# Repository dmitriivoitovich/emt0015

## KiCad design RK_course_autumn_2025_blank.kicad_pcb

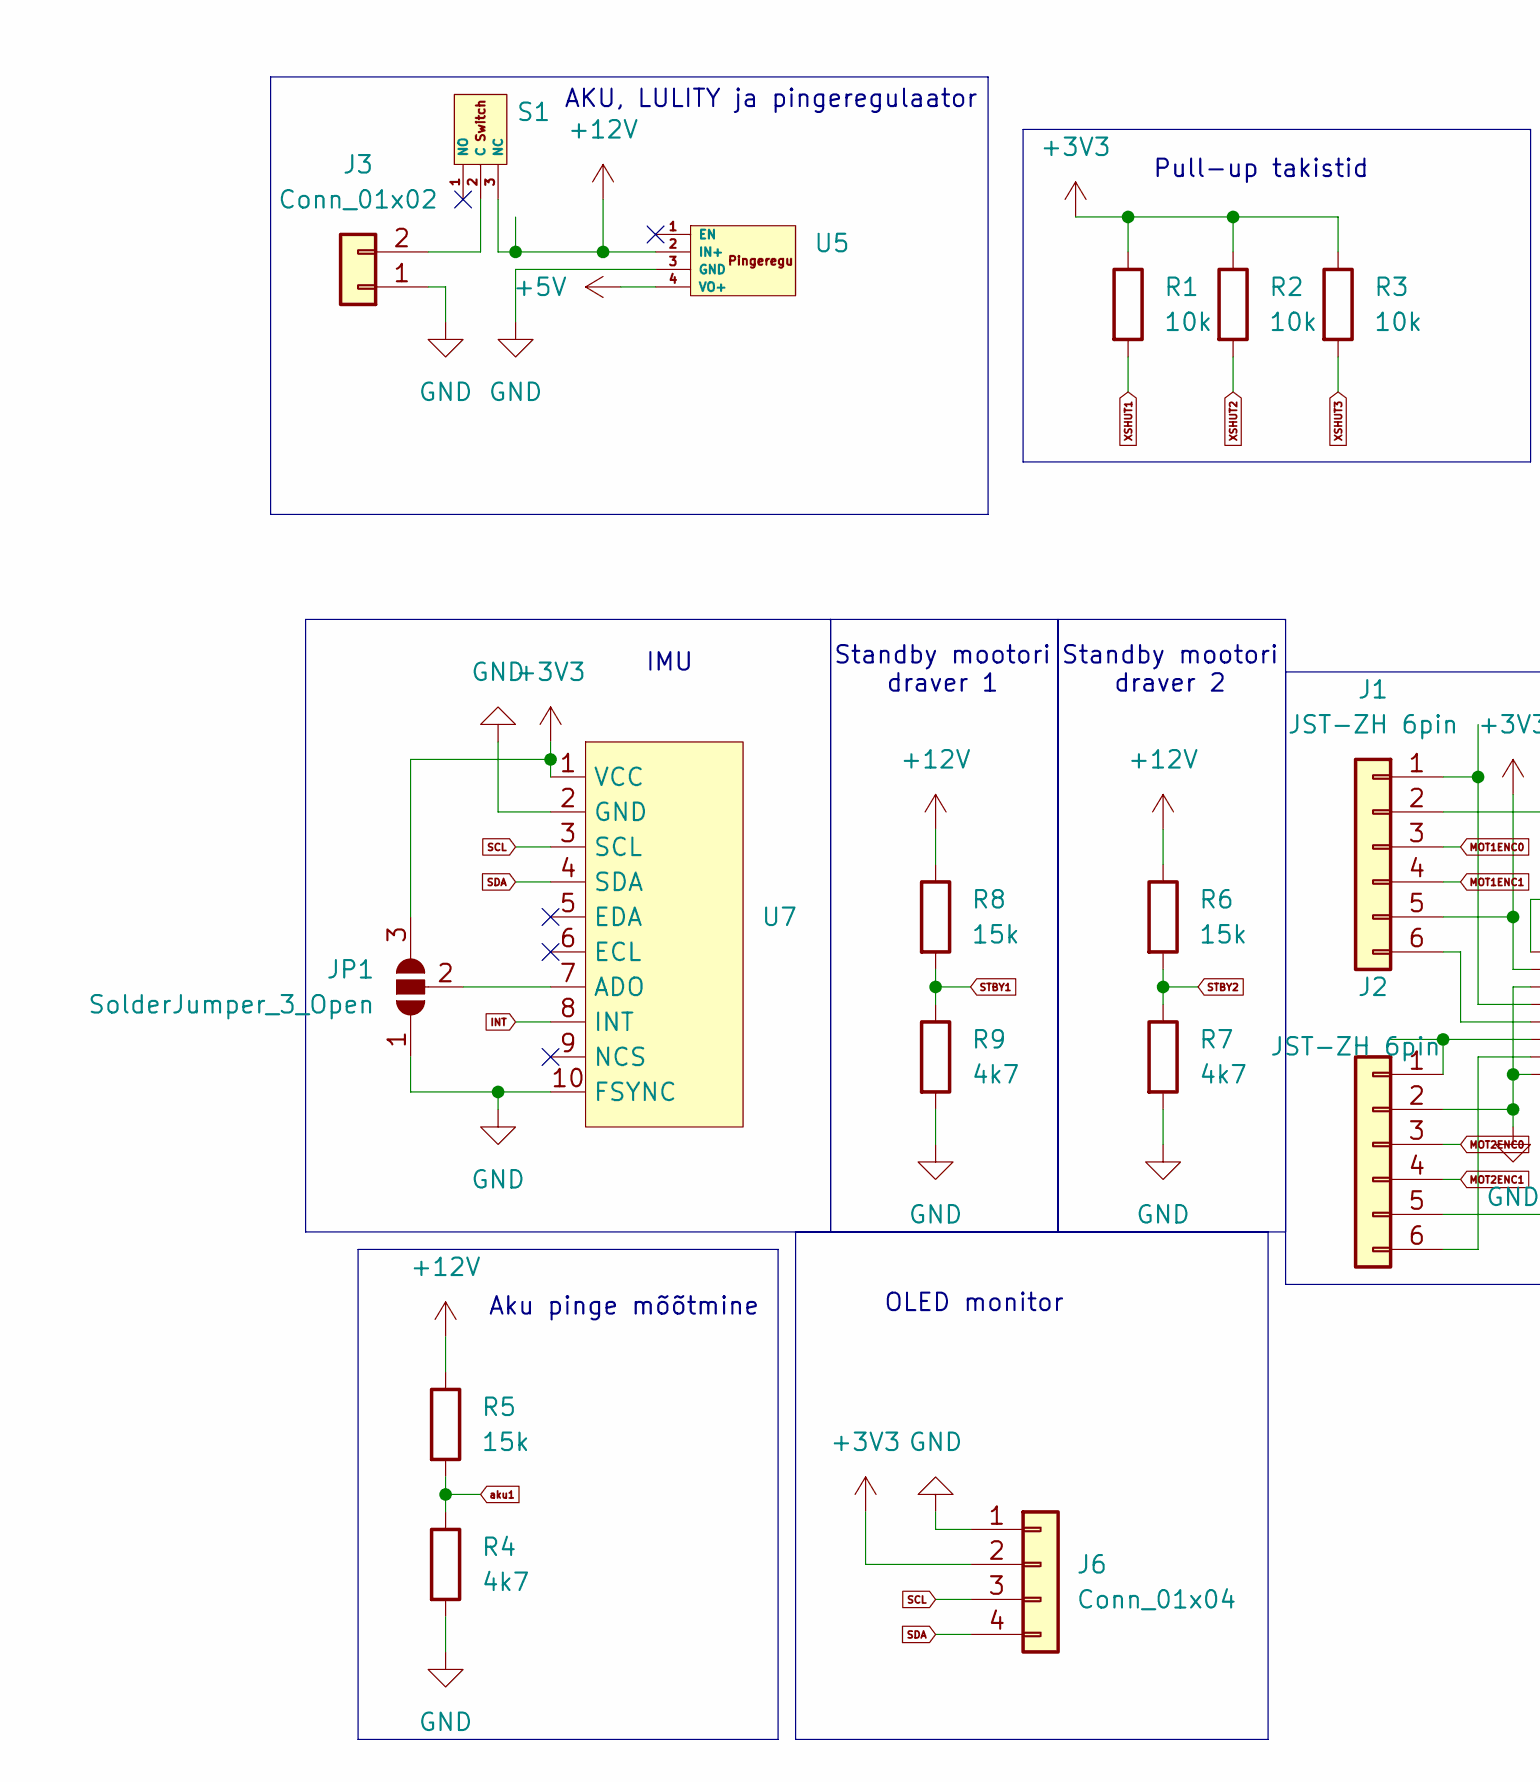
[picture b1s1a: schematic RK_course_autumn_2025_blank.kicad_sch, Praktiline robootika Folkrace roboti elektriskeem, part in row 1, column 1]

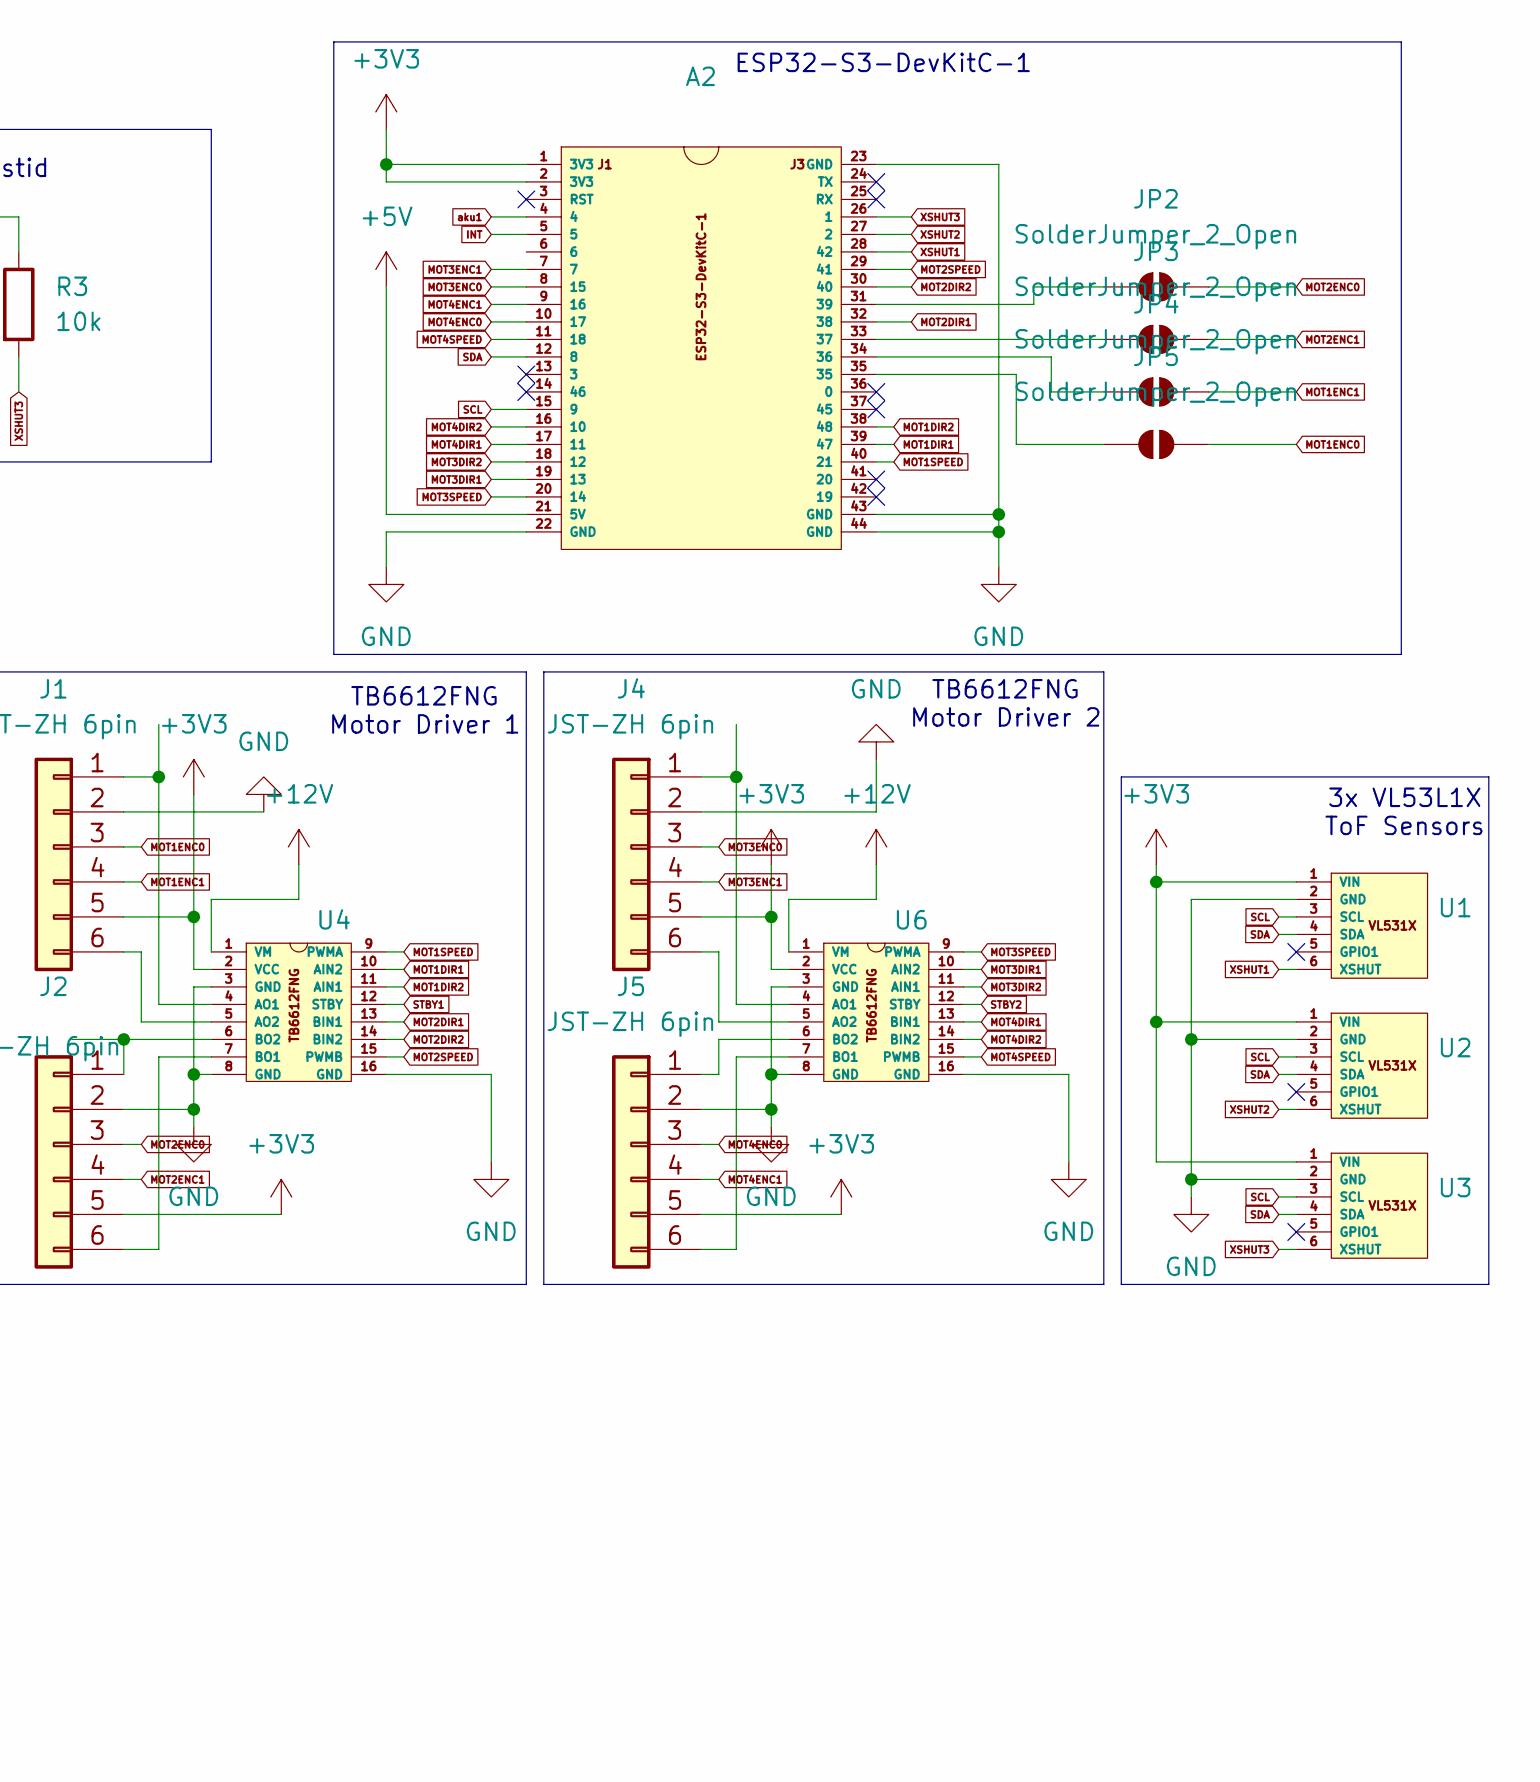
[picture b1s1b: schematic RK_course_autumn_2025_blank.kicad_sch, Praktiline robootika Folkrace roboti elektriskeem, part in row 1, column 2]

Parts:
A2: ESP32-S3-DevKitC-1
J1, J2, J4, J5: JST-ZH 6pin; JST_ZH_B6B-ZR_1x06_P1.50mm_Vertical
J3: Conn_01x02; AMASS_XT30PW-M_1x02_P2.50mm_Horizontal
J6: Conn_01x04; PinHeader_1x04_P2.54mm_Vertical
JP1: SolderJumper_3_Open; SolderJumper-3_P1.3mm_Open_RoundedPad1.0x1.5mm
JP2, JP3, JP4, JP5: SolderJumper_2_Open; SolderJumper-2_P1.3mm_Open_RoundedPad1.0x1.5mm
R1, R2, R3: 10k; R_0603_1608Metric_Pad0.98x0.95mm_HandSolder
R4, R7, R9: 4k7; R_0603_1608Metric_Pad0.98x0.95mm_HandSolder
R5, R6, R8: 15k; R_0603_1608Metric_Pad0.98x0.95mm_HandSolder
S1: 6A125VAC_NO-NO_SWITCH
U1, U2, U3: VL531X_KAUGUS_SENSOR
U4, U6: TB6612FNG_DUAL_MOTOR_DRIVER_RED
U5: PINGEREGU
U7: IMU

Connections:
+3V3: A2.1 (3V3), A2.2 (3V3), J1.5, J2.5, J4.5, J5.5, J6.2, JP1.3 (B), R1.1, R2.1, R3.1, U1.1 (VIN), U2.1 (VIN), U3.1 (VIN), U4.2 (VCC), U6.2 (VCC), U7.1 (VCC)
+5V: A2.21 (5V), U5.4 (VO+)
+12V: R5.1, R6.1, R8.1, S1.3 (NC), U4.1 (VM), U5.2 (IN+), U6.1 (VM)
GND: A2.22 (GND), A2.23 (GND), A2.43 (GND), A2.44 (GND), J1.2, J2.2, J3.1, J4.2, J5.2, J6.1, JP1.1 (A), R4.2, R7.2, R9.2, U1.2 (GND), U2.2 (GND), U3.2 (GND), U4.3 (GND), U4.8 (GND), U4.16 (GND), U5.3 (GND), U6.3 (GND), U6.8 (GND), U6.16 (GND), U7.2 (GND), U7.10 (FSYNC)
INT: A2.5, U7.8 (INT)
MOT1DIR1: A2.39 (47), U4.10 (AIN2)
MOT1DIR2: A2.38 (48), U4.11 (AIN1)
MOT1ENC0: J1.3, JP5.2 (B)
MOT1ENC1: J1.4, JP4.2 (B)
MOT1SPEED: A2.40 (21), U4.9 (PWMA)
MOT2DIR1: A2.32 (38), U4.13 (BIN1)
MOT2DIR2: A2.30 (40), U4.14 (BIN2)
MOT2ENC0: J2.3, JP2.2 (B)
MOT2ENC1: J2.4, JP3.2 (B)
MOT2SPEED: A2.29 (41), U4.15 (PWMB)
MOT3DIR1: A2.19 (13), U6.10 (AIN2)
MOT3DIR2: A2.18 (12), U6.11 (AIN1)
MOT3ENC0: A2.8 (15), J4.3
MOT3ENC1: A2.7, J4.4
MOT3SPEED: A2.20 (14), U6.9 (PWMA)
MOT4DIR1: A2.17 (11), U6.13 (BIN1)
MOT4DIR2: A2.16 (10), U6.14 (BIN2)
MOT4ENC0: A2.10 (17), J5.3
MOT4ENC1: A2.9 (16), J5.4
MOT4SPEED: A2.11 (18), U6.15 (PWMB)
unnamed: A2.34 (36), JP4.1 (A)
unnamed: A2.33 (37), JP3.1 (A)
unnamed: A2.31 (39), JP2.1 (A)
unnamed: J1.1, U4.4 (AO1)
unnamed: J1.6, U4.5 (AO2)
unnamed: J2.1, U4.6 (BO2)
unnamed: J2.6, U4.7 (BO1)
unnamed: J3.2, S1.2 (C)
unnamed: J4.1, U6.4 (AO1)
unnamed: J4.6, U6.5 (AO2)
unnamed: J5.1, U6.6 (BO2)
unnamed: J5.6, U6.7 (BO1)
unnamed: JP1.2 (C), U7.7 (ADO)
unnamed: A2.35, JP5.1 (A)
SCL: A2.15 (9), J6.3, U1.3 (SCL), U2.3 (SCL), U3.3 (SCL), U7.3 (SCL)
SDA: A2.12 (8), J6.4, U1.4 (SDA), U2.4 (SDA), U3.4 (SDA), U7.4 (SDA)
STBY1: R8.2, R9.1, U4.12 (STBY)
STBY2: R6.2, R7.1, U6.12 (STBY)
XSHUT1: A2.28 (42), R1.2, U1.6 (XSHUT)
XSHUT2: A2.27 (2), R2.2, U2.6 (XSHUT)
XSHUT3: A2.26 (1), R3.2, U3.6 (XSHUT)
aku1: A2.4, R4.1, R5.2

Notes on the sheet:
TB6612FNG Motor Driver 1
Standby mootori draver 2
Standby mootori draver 1
AKU, LULITY ja pingeregulaator
Pull-up takistid
TB6612FNG Motor Driver 2
IMU
Aku pinge mõõtmine
ESP32-S3-DevKitC-1
3x VL53L1X ToF Sensors
OLED monitor

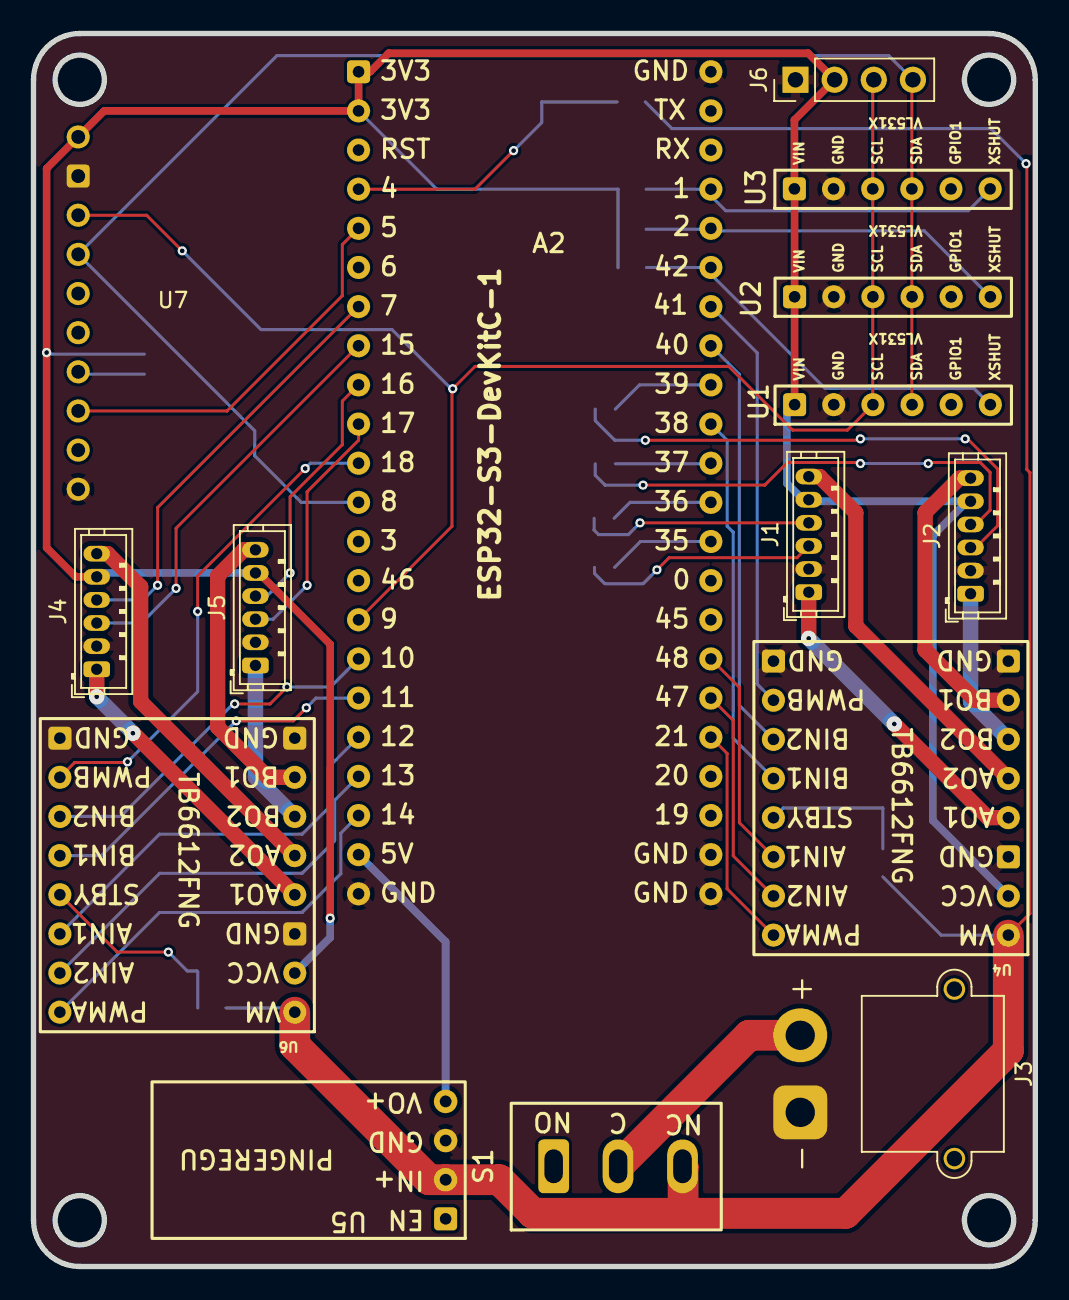
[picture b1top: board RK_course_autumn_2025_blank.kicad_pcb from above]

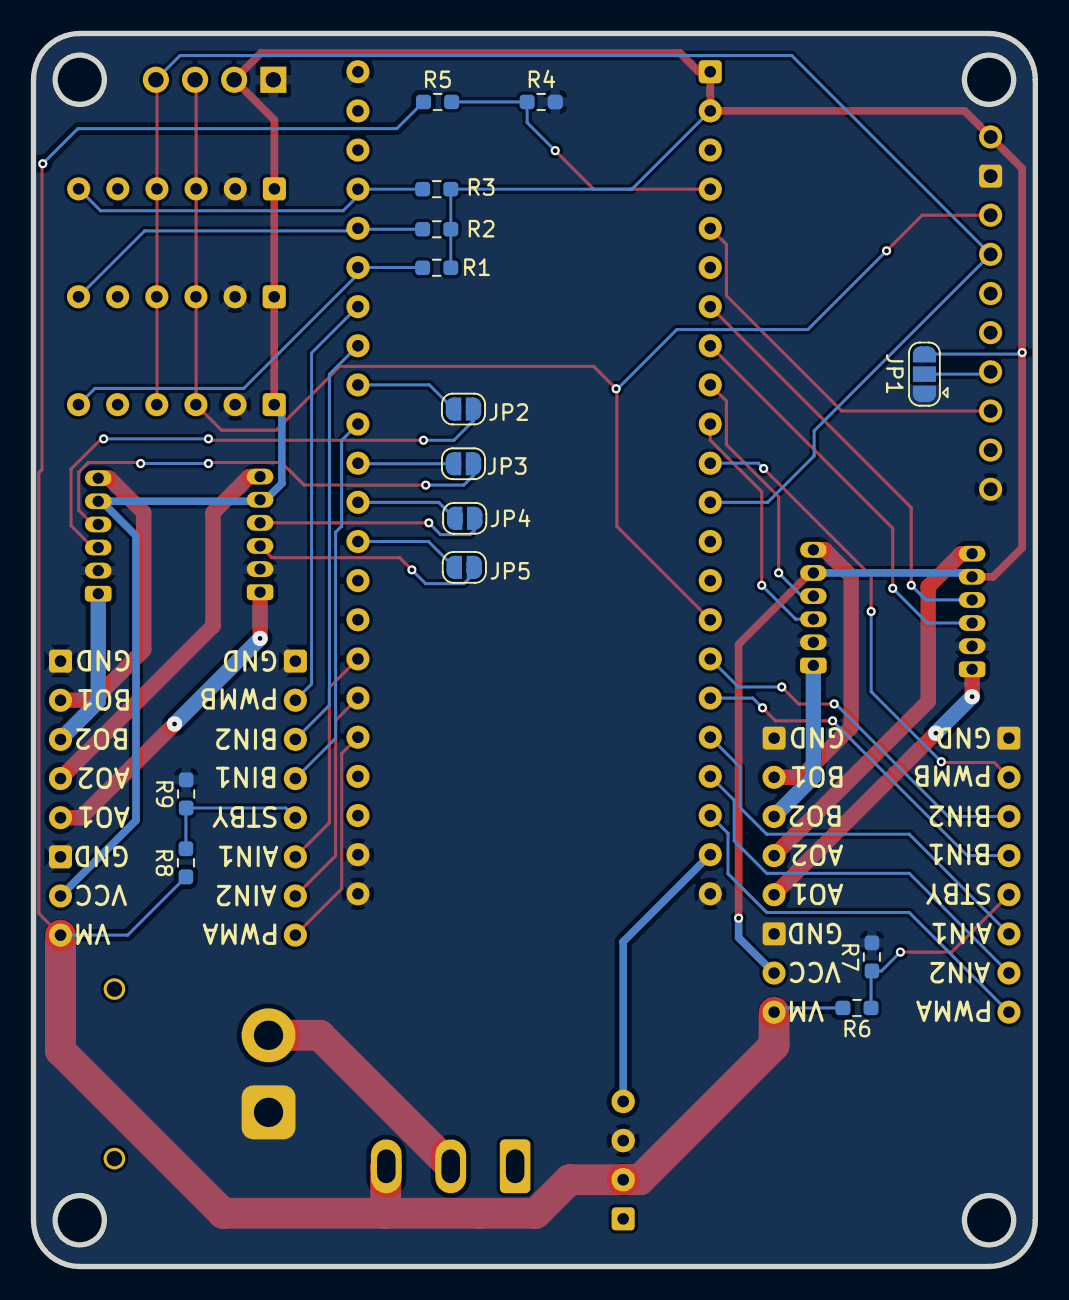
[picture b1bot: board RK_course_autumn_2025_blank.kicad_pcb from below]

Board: 2 copper layers, 65.0 x 80.0 mm, 29 parts (14 on the bottom side), 47 nets.

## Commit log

2025-10-09 ignore backups
2025-10-09 Add local copies to change models
2025-10-09 Added IMU footprint, model, schematic. Updated the schematic and PCB a bit
2025-10-09 Better placement for 12V
2025-10-11 Fixed pull-up resistors, added battery voltage measurement, better pin connection layout
2025-10-11 Added traces to PCB to see if possible. Has to be done again.
2025-10-20 added connector for oled monitor, fixed i2c pins
2025-10-22 arduino code
2025-10-22 Add motor control functions and initial project files
2025-10-22 Add gitignore
2025-10-28 new schematic, PCB tracks not final
2025-10-29 now with tracks
2025-11-12 Refactor motor control functions to accept separate left and right speed parameters; enhance state machine logic in main sketch
2025-11-12 Refactor speed control logic to use filtered sensor data; adjust speed parameters for improved maneuverability
2025-11-12 Refactor sensitivity calculation for improved clarity
2025-11-26 Refactor sensor reading and state handling logic for improved maneuverability
2025-11-26 Refactor control logic to improve speed adjustment and state handling using PID principles
2025-11-28 PID fix
2025-11-29 Refactor sensor control logic to enhance speed management and state handling
2025-11-29 Refactor speed control parameters and sensor calculations for improved maneuverability
